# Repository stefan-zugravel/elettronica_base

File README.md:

# elettronica_base

## lab0
Keypad PCB with KiCAD

## lab1
Current sensing PCB

## lab2
Insert an FPGA in your PCB (quick preview)

## lab3
Inverter, logic gates and mux in VHDL

## lab4
Length tuning and de-skewing in KiCAD

## lab5
BCD counter in VHDL and differnt ways of dividing clock

## lab6
LTspice labs

## lab7
FIR filter and DDS compiler using FPGA

## lab8
FPGA PWM controller used for LED breathing effect

## lab9
A simple FSM in VHDL

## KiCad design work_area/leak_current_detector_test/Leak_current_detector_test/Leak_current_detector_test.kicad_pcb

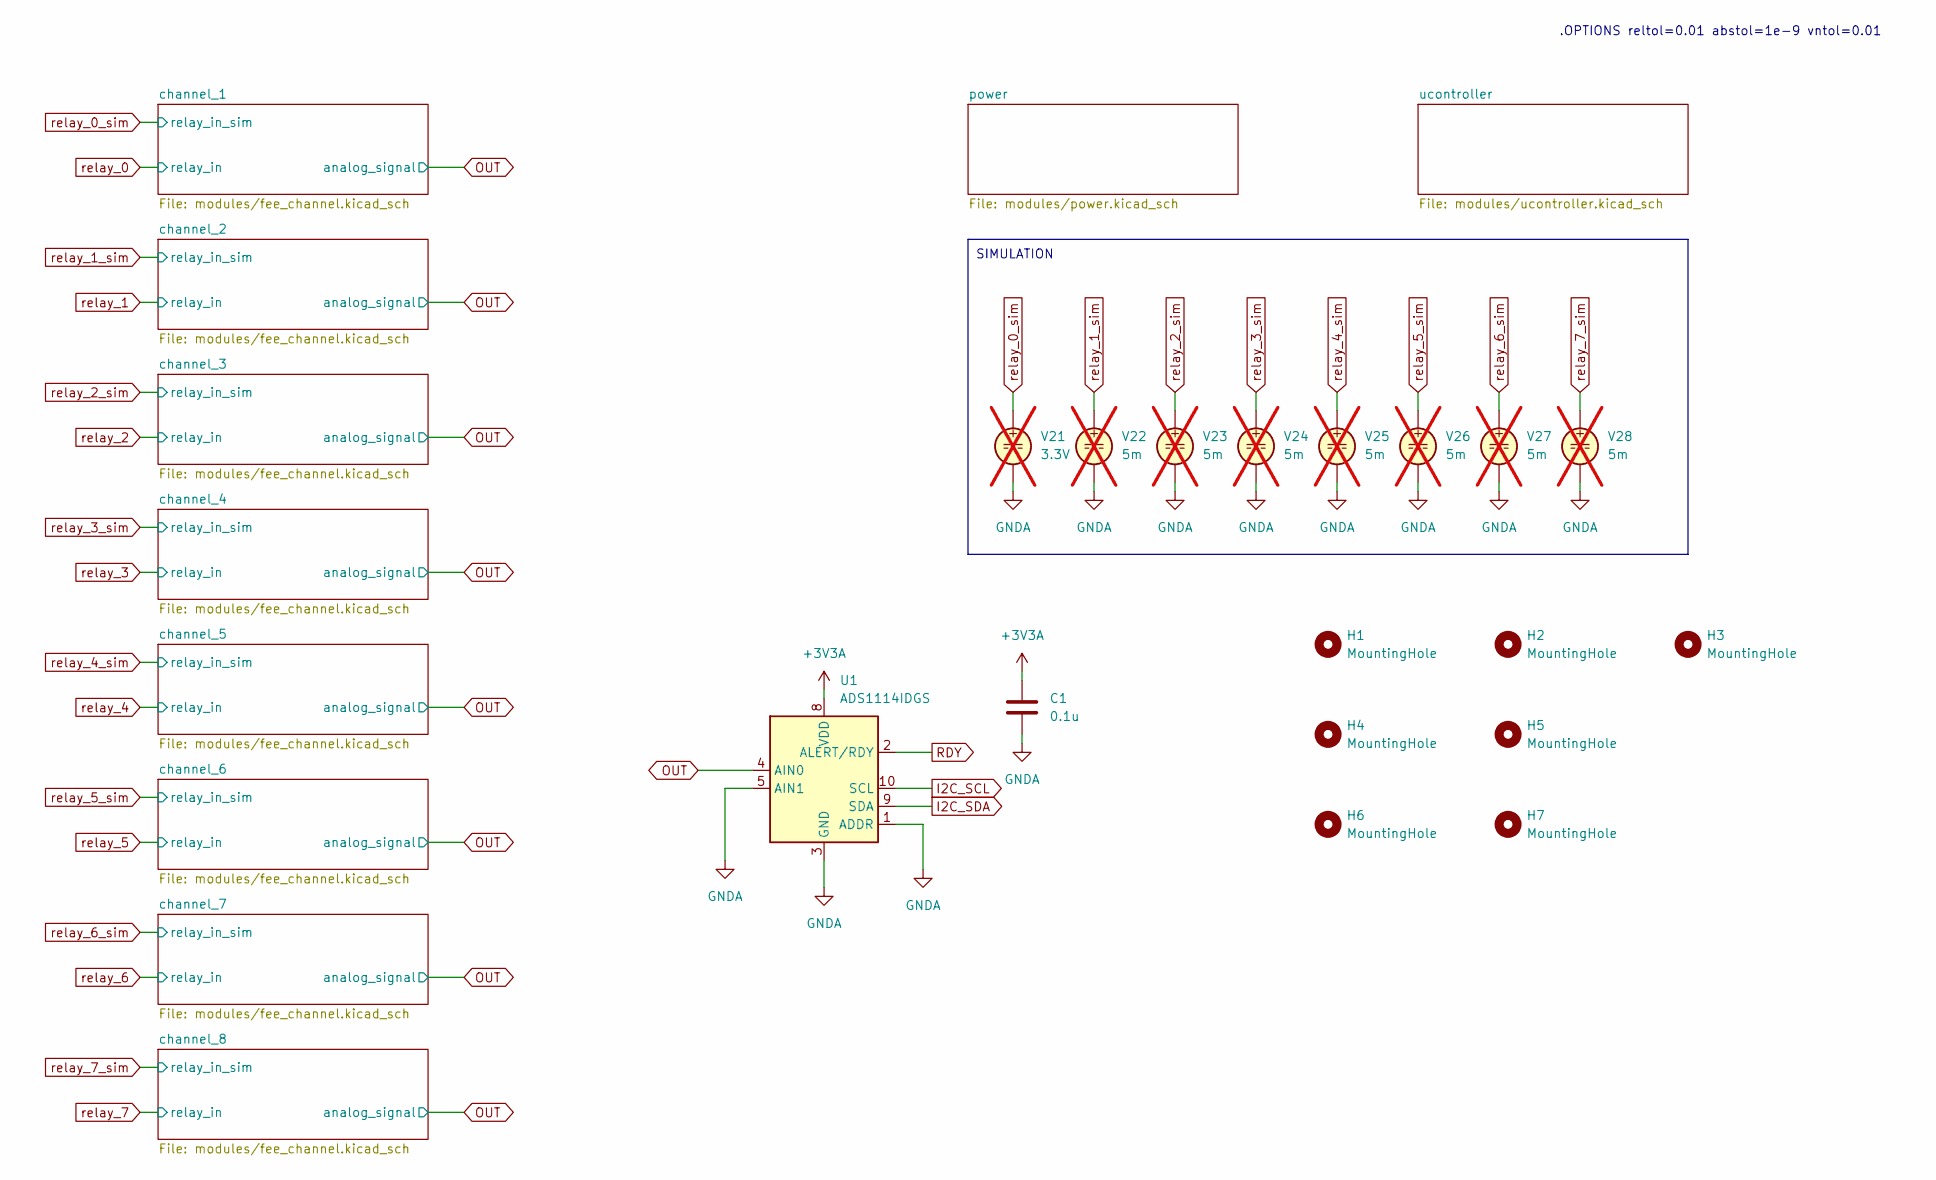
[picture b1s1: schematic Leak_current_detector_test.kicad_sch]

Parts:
C1: 0.1u; C_0603_1608Metric
H1, H2, H3: MountingHole; ToolingHole_1.152mm
H4, H5, H6, H7: MountingHole; MountingHole_3.2mm_M3
U1: ADS1114IDGS; TSSOP-10_3x3mm_P0.5mm
V21: 3.3V; not fitted
V22, V23, V24, V25, V26, V27, V28: 5m; not fitted

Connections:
+3V3A: C1.1, U1.8 (VDD); also elsewhere on the board
GNDA: C1.2, U1.1 (ADDR), U1.3 (GND), U1.5 (AIN1), V21.2, V22.2, V23.2, V24.2, V25.2, V26.2, V27.2, V28.2; also elsewhere on the board
I2C_SCL: U1.10 (SCL); also elsewhere on the board
I2C_SDA: U1.9 (SDA); also elsewhere on the board
OUT: U1.4 (AIN0); also elsewhere on the board
RDY: U1.2 (ALERT/RDY); also elsewhere on the board

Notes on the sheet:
SIMULATION
.OPTIONS reltol=0.01 abstol=1e-9 vntol=0.01

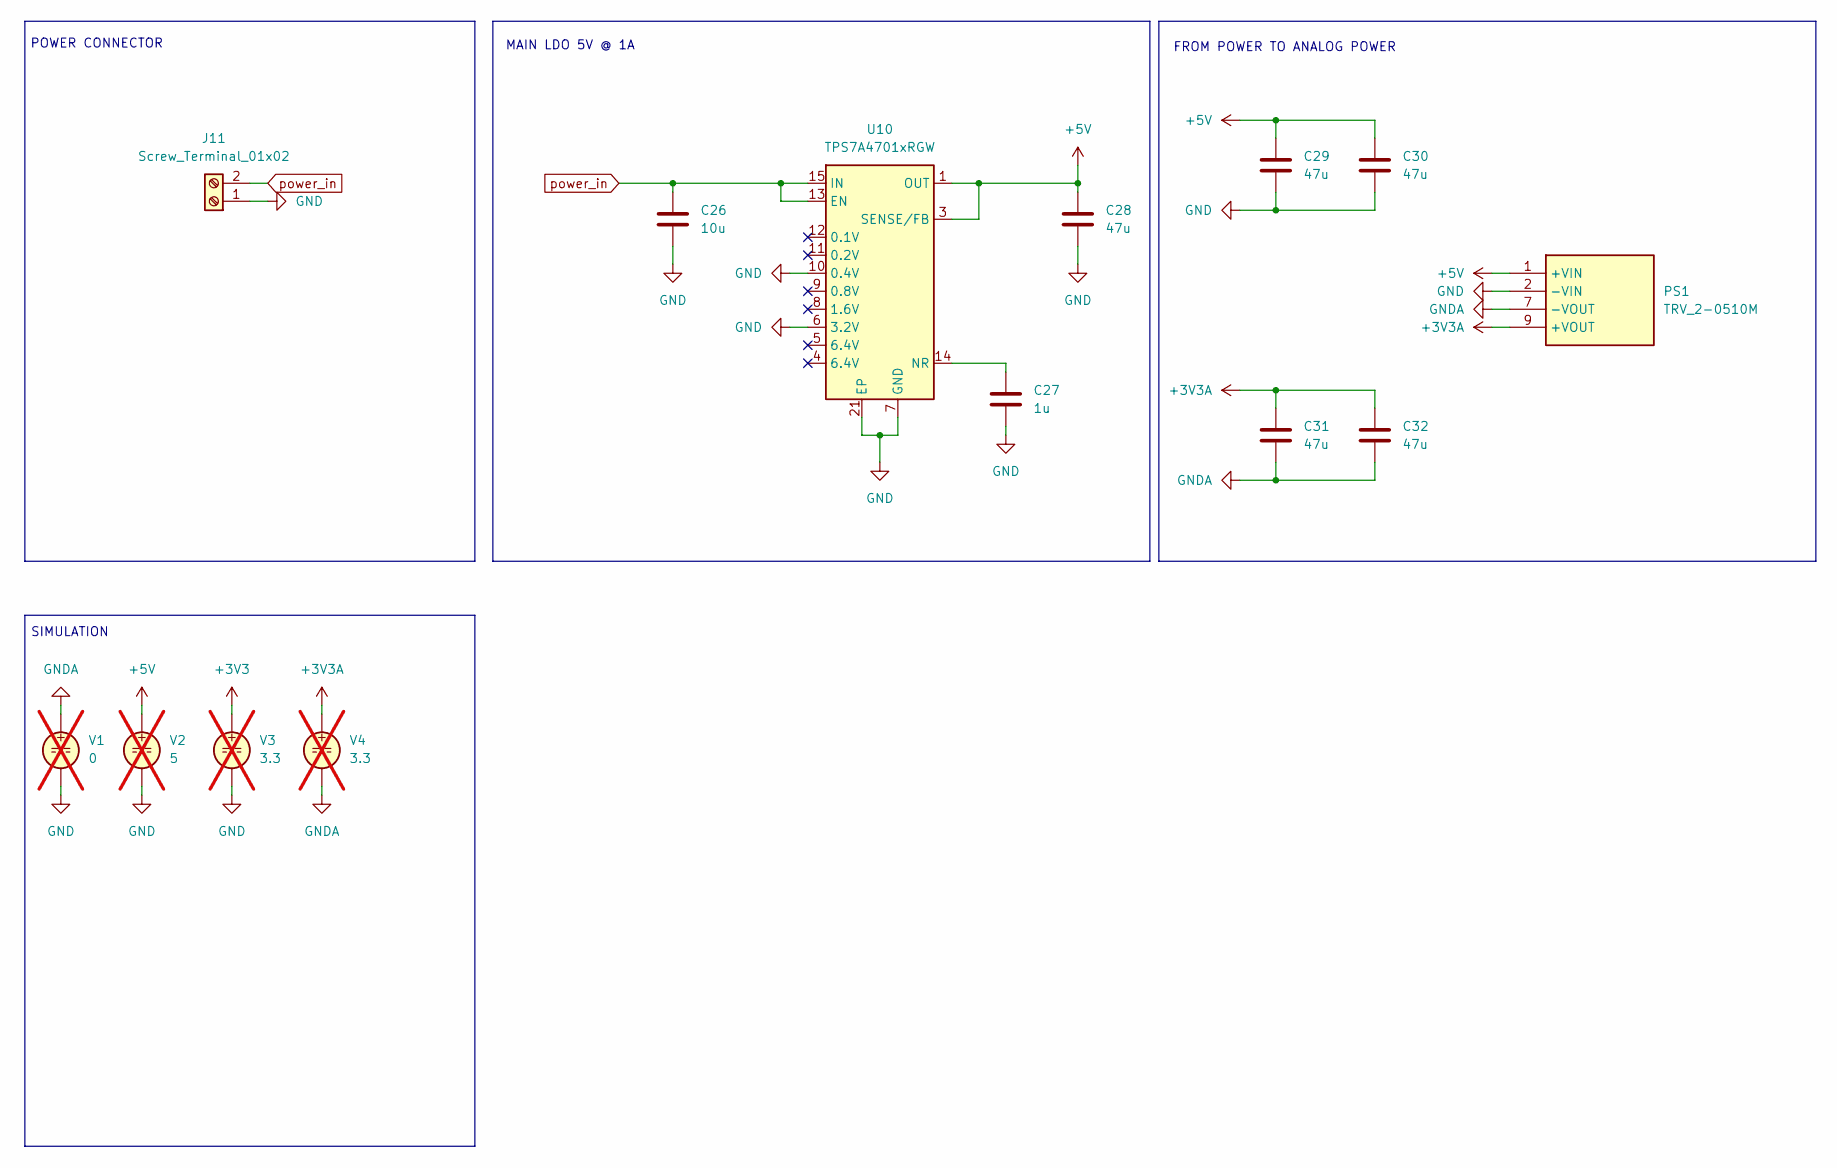
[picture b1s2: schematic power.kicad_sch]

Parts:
C26: 10u; C_0603_1608Metric
C27: 1u; C_0603_1608Metric
C28, C29, C30, C31, C32: 47u; C_0805_2012Metric
J11: Screw_Terminal_01x02; PhoenixContact_MSTBA_2,5_2-G-5,08_1x02_P5.08mm_Horizontal
PS1: TRV_2-0510M; TRV20510M; Mouser Part Number 495-TRV2-0510M
U10: TPS7A4701xRGW; Texas_RGW0020A_VQFN-20-1EP_5x5mm_P0.65mm_EP3.15x3.15mm_Ther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
V1: 0; not fitted
V2: 5; not fitted
V3, V4: 3.3; not fitted

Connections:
+3V3A: C31.1, C32.1, PS1.9 (+VOUT), V4.1; also elsewhere on the board
+5V: C28.1, C29.1, C30.1, PS1.1 (+VIN), U10.1 (OUT), U10.3 (SENSE/FB), U10.20 (OUT), V2.1; also elsewhere on the board
GND: C26.2, C27.2, C28.2, C29.2, C30.2, J11.1, PS1.2 (-VIN), U10.6 (3.2V), U10.7 (GND), U10.10 (0.4V), U10.21 (EP), V1.2, V2.2, V3.2; also elsewhere on the board
GNDA: C31.2, C32.2, PS1.7 (-VOUT), V1.1, V4.2; also elsewhere on the board
unnamed: C27.1, U10.14 (NR)
power_in: C26.1, J11.2, U10.13 (EN), U10.15 (IN), U10.16 (IN)

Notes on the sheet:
FROM POWER TO ANALOG POWER
MAIN LDO 5V @ 1A
POWER CONNECTOR
SIMULATION

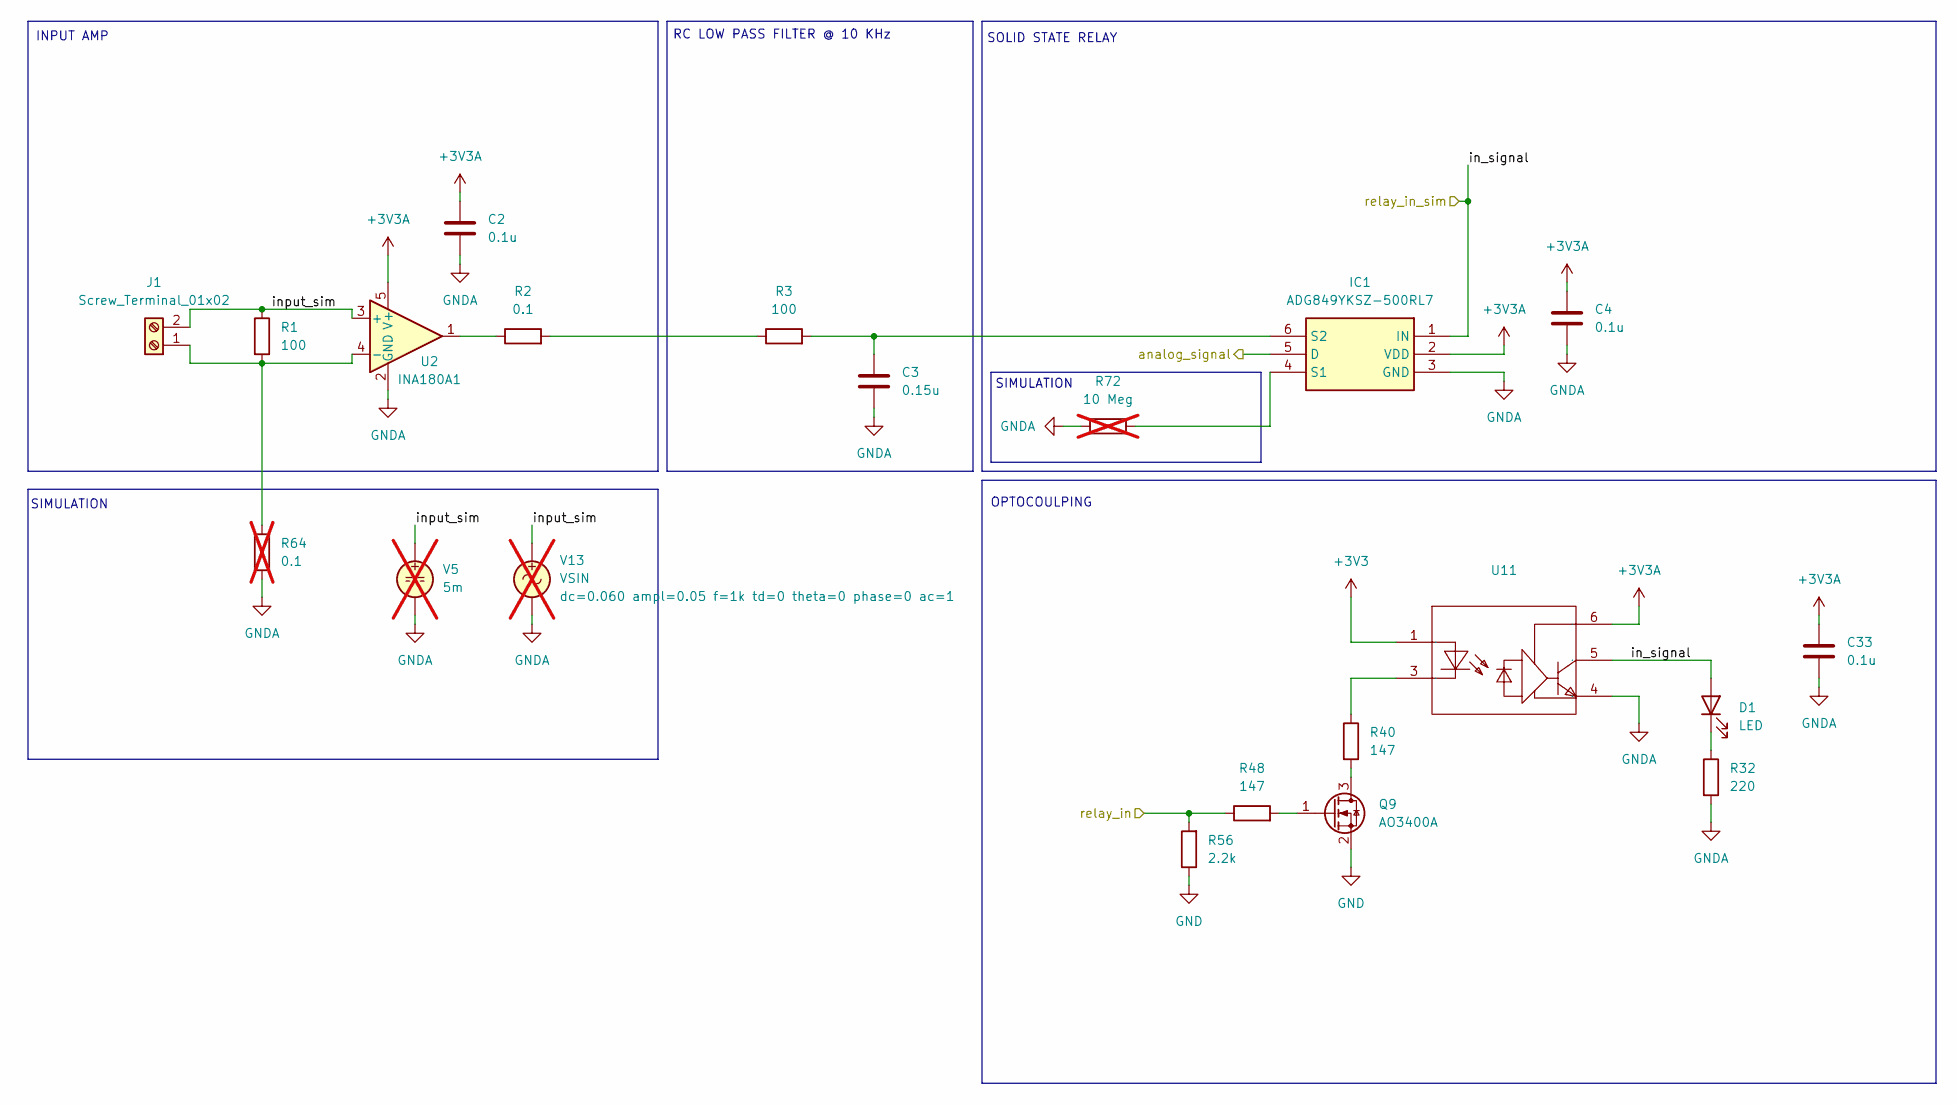
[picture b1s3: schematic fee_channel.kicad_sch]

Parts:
C2, C4, C33: 0.1u; C_0603_1608Metric
C3: 0.15u; C_0603_1608Metric
D1: LED; LED_0603_1608Metric
IC1: ADG849YKSZ-500RL7; SOT65P210X110-6N; Mouser Part Number 584-ADG849YKSZ-500R7
J1: Screw_Terminal_01x02; PhoenixContact_MCV_1,5_2-G-3.5_1x02_P3.50mm_Vertical
Q9: AO3400A; SOT-23
R1, R3: 100; R_0603_1608Metric
R2: 0.1; R_0603_1608Metric
R32: 220; R_0603_1608Metric
R40, R48: 147; R_0603_1608Metric
R56: 2.2k; R_0603_1608Metric
R64: 0.1; not fitted
R72: 10 Meg; not fitted
U2: INA180A1; SOT-23-5
U11: OPTO-SMD-5_L3.7-W4.6-P1.27-LS7.0-BR; Manufacturer Part TLP2362(TPL,E; LCSC Part Name DC输入 1通道 隔离电压(rms):3750V
V5: 5m; not fitted
V13: VSIN; not fitted

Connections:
+3V3: U11.1; also elsewhere on the board
+3V3A: C2.1, C4.1, C33.1, IC1.2 (VDD), U2.5 (V+), U11.6; also elsewhere on the board
/channel_1/input_sim: J1.2, R1.1, U2.3 (+)
GND: Q9.2 (S), R56.1; also elsewhere on the board
GNDA: C2.2, C3.2, C4.2, C33.2, IC1.3 (GND), R32.2, R64.2, R72.1, U2.2 (GND), U11.4, V5.2, V13.2; also elsewhere on the board
unnamed: D1.1 (K), R32.1
unnamed: C3.1, IC1.6 (S2), R3.2
unnamed: J1.1, R1.2, U2.4 (-)
unnamed: Q9.3 (D), R40.2
unnamed: Q9.1 (G), R48.2
unnamed: R2.1, U2.1
unnamed: R2.2, R3.1
unnamed: R40.1, U11.3
OUT: IC1.5 (D); also elsewhere on the board
relay_0: R48.1, R56.2; also elsewhere on the board
relay_0_sim: D1.2 (A), IC1.1 (IN), U11.5

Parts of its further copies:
C5, C7, C8, C10, C11, C13, C14, C16, C17, C19, C20, C22, C23, C25, C34, C35, C36, C37, C38, C39, C40: 0.1u; C_0603_1608Metric
C6, C9, C12, C15, C18, C21, C24: 0.15u; C_0603_1608Metric
D2, D3, D4, D5, D6, D7, D8: LED; LED_0603_1608Metric
IC2, IC3, IC4, IC5, IC6, IC7, IC8: ADG849YKSZ-500RL7; SOT65P210X110-6N; Mouser Part Number 584-ADG849YKSZ-500R7
J2, J3, J4, J5, J6, J7, J8: Screw_Terminal_01x02; PhoenixContact_MCV_1,5_2-G-3.5_1x02_P3.50mm_Vertical
Q10, Q11, Q12, Q13, Q14, Q15, Q16: AO3400A; SOT-23
R4, R6, R7, R9, R10, R12, R13, R15, R16, R18, R19, R21, R22, R24: 100; R_0603_1608Metric
R5, R8, R11, R14, R17, R20, R23: 0.1; R_0603_1608Metric
R33, R34, R35, R36, R37, R38, R39: 220; R_0603_1608Metric
R41, R42, R43, R44, R45, R46, R47, R49, R50, R51, R52, R53, R54, R55: 147; R_0603_1608Metric
R57, R58, R59, R60, R61, R62, R63: 2.2k; R_0603_1608Metric
U3, U4, U5, U6, U7, U8, U9: INA180A1; SOT-23-5
U12, U13, U14, U15, U16, U17, U18: OPTO-SMD-5_L3.7-W4.6-P1.27-LS7.0-BR; Manufacturer Part TLP2362(TPL,E; LCSC Part Name DC输入 1通道 隔离电压(rms):3750V

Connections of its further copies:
+3V3: U12.1, U13.1, U14.1, U15.1, U16.1, U17.1, U18.1; also elsewhere on the board
+3V3A: C5.1, C7.1, C8.1, C10.1, C11.1, C13.1, C14.1, C16.1, C17.1, C19.1, C20.1, C22.1, C23.1, C25.1, C34.1, C35.1, C36.1, C37.1, C38.1, C39.1, C40.1, IC2.2 (VDD), IC3.2 (VDD), IC4.2 (VDD), IC5.2 (VDD), IC6.2 (VDD), IC7.2 (VDD), IC8.2 (VDD), U3.5 (V+), U4.5 (V+), U5.5 (V+), U6.5 (V+), U7.5 (V+), U8.5 (V+), U9.5 (V+), U12.6, U13.6, U14.6, U15.6, U16.6, U17.6, U18.6; also elsewhere on the board
/channel_2/input_sim: J2.2, R4.1, U3.3 (+)
/channel_3/input_sim: J3.2, R7.1, U4.3 (+)
/channel_4/input_sim: J4.2, R10.1, U5.3 (+)
/channel_5/input_sim: J5.2, R13.1, U6.3 (+)
/channel_6/input_sim: J6.2, R16.1, U7.3 (+)
/channel_7/input_sim: J7.2, R19.1, U8.3 (+)
/channel_8/input_sim: J8.2, R22.1, U9.3 (+)
GND: Q10.2 (S), Q11.2 (S), Q12.2 (S), Q13.2 (S), Q14.2 (S), Q15.2 (S), Q16.2 (S), R57.1, R58.1, R59.1, R60.1, R61.1, R62.1, R63.1; also elsewhere on the board
GNDA: C5.2, C6.2, C7.2, C8.2, C9.2, C10.2, C11.2, C12.2, C13.2, C14.2, C15.2, C16.2, C17.2, C18.2, C19.2, C20.2, C21.2, C22.2, C23.2, C24.2, C25.2, C34.2, C35.2, C36.2, C37.2, C38.2, C39.2, C40.2, IC2.3 (GND), IC3.3 (GND), IC4.3 (GND), IC5.3 (GND), IC6.3 (GND), IC7.3 (GND), IC8.3 (GND), R33.2, R34.2, R35.2, R36.2, R37.2, R38.2, R39.2, U3.2 (GND), U4.2 (GND), U5.2 (GND), U6.2 (GND), U7.2 (GND), U8.2 (GND), U9.2 (GND), U12.4, U13.4, U14.4, U15.4, U16.4, U17.4, U18.4; also elsewhere on the board
unnamed: D2.1 (K), R33.1
unnamed: D3.1 (K), R34.1
unnamed: D4.1 (K), R35.1
unnamed: D5.1 (K), R36.1
unnamed: D6.1 (K), R37.1
unnamed: D7.1 (K), R38.1
unnamed: D8.1 (K), R39.1
unnamed: C6.1, IC2.6 (S2), R6.2
unnamed: C9.1, IC3.6 (S2), R9.2
unnamed: C12.1, IC4.6 (S2), R12.2
unnamed: C15.1, IC5.6 (S2), R15.2
unnamed: C18.1, IC6.6 (S2), R18.2
unnamed: C21.1, IC7.6 (S2), R21.2
unnamed: C24.1, IC8.6 (S2), R24.2
unnamed: J2.1, R4.2, U3.4 (-)
unnamed: J3.1, R7.2, U4.4 (-)
unnamed: J4.1, R10.2, U5.4 (-)
unnamed: J5.1, R13.2, U6.4 (-)
unnamed: J6.1, R16.2, U7.4 (-)
unnamed: J7.1, R19.2, U8.4 (-)
unnamed: J8.1, R22.2, U9.4 (-)
unnamed: Q10.3 (D), R41.2
unnamed: Q10.1 (G), R49.2
unnamed: Q11.3 (D), R42.2
unnamed: Q11.1 (G), R50.2
unnamed: Q12.3 (D), R43.2
unnamed: Q12.1 (G), R51.2
unnamed: Q13.3 (D), R44.2
unnamed: Q13.1 (G), R52.2
unnamed: Q14.3 (D), R45.2
unnamed: Q14.1 (G), R53.2
unnamed: Q15.3 (D), R46.2
unnamed: Q15.1 (G), R54.2
unnamed: Q16.3 (D), R47.2
unnamed: Q16.1 (G), R55.2
unnamed: R5.1, U3.1
unnamed: R5.2, R6.1
unnamed: R8.1, U4.1
unnamed: R8.2, R9.1
unnamed: R11.1, U5.1
unnamed: R11.2, R12.1
unnamed: R14.1, U6.1
unnamed: R14.2, R15.1
unnamed: R17.1, U7.1
unnamed: R17.2, R18.1
unnamed: R20.1, U8.1
unnamed: R20.2, R21.1
unnamed: R23.1, U9.1
unnamed: R23.2, R24.1
unnamed: R41.1, U12.3
unnamed: R42.1, U13.3
unnamed: R43.1, U14.3
unnamed: R44.1, U15.3
unnamed: R45.1, U16.3
unnamed: R46.1, U17.3
unnamed: R47.1, U18.3
OUT: IC2.5 (D), IC3.5 (D), IC4.5 (D), IC5.5 (D), IC6.5 (D), IC7.5 (D), IC8.5 (D); also elsewhere on the board
relay_1: R49.1, R57.2; also elsewhere on the board
relay_1_sim: D2.2 (A), IC2.1 (IN), U12.5
relay_2: R50.1, R58.2; also elsewhere on the board
relay_2_sim: D3.2 (A), IC3.1 (IN), U13.5
relay_3: R51.1, R59.2; also elsewhere on the board
relay_3_sim: D4.2 (A), IC4.1 (IN), U14.5
relay_4: R52.1, R60.2; also elsewhere on the board
relay_4_sim: D5.2 (A), IC5.1 (IN), U15.5
relay_5: R53.1, R61.2; also elsewhere on the board
relay_5_sim: D6.2 (A), IC6.1 (IN), U16.5
relay_6: R54.1, R62.2; also elsewhere on the board
relay_6_sim: D7.2 (A), IC7.1 (IN), U17.5
relay_7: R55.1, R63.2; also elsewhere on the board
relay_7_sim: D8.2 (A), IC8.1 (IN), U18.5

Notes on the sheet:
SIMULATION
RC LOW PASS FILTER @ 10 KHz
INPUT AMP
SOLID STATE RELAY
OPTOCOULPING

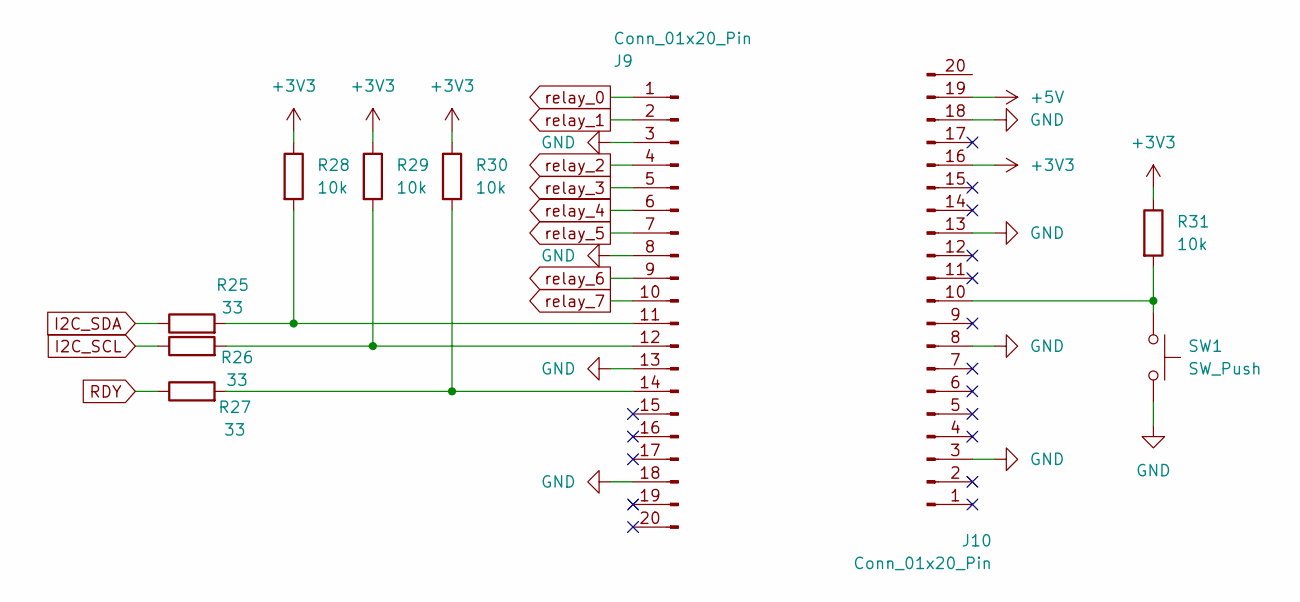
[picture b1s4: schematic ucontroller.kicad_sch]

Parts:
J9, J10: Conn_01x20_Pin; PinHeader_1x20_P2.54mm_Vertical
R25, R26, R27: 33; R_0603_1608Metric
R28, R29, R30, R31: 10k; R_0603_1608Metric
SW1: SW_Push; SW_PUSH_6mm_H5mm

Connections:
+3V3: J10.16, R28.1, R29.1, R30.1, R31.1; also elsewhere on the board
+5V: J10.19; also elsewhere on the board
GND: J9.3, J9.8, J9.13, J9.18, J10.3, J10.8, J10.13, J10.18, SW1.2; also elsewhere on the board
I2C_SCL: R26.1; also elsewhere on the board
I2C_SDA: R25.1; also elsewhere on the board
unnamed: J9.11, R25.2, R28.2
unnamed: J9.12, R26.2, R29.2
unnamed: J9.14, R27.2, R30.2
unnamed: J10.10, R31.2, SW1.1
RDY: R27.1; also elsewhere on the board
relay_0: J9.1; also elsewhere on the board
relay_1: J9.2; also elsewhere on the board
relay_2: J9.4; also elsewhere on the board
relay_3: J9.5; also elsewhere on the board
relay_4: J9.6; also elsewhere on the board
relay_5: J9.7; also elsewhere on the board
relay_6: J9.9; also elsewhere on the board
relay_7: J9.10; also elsewhere on the board

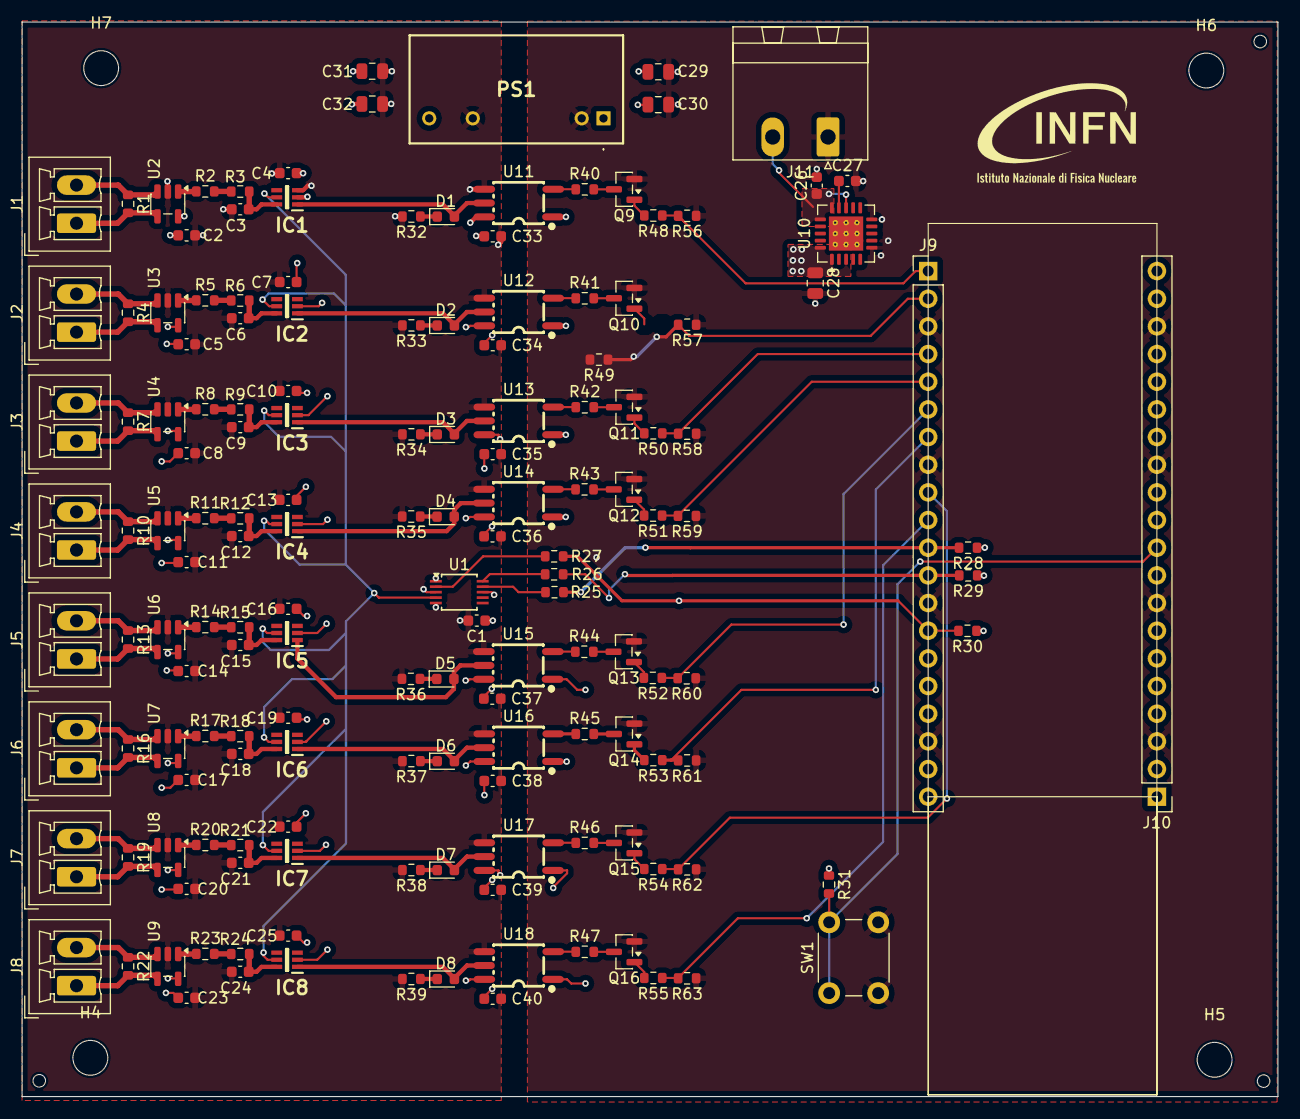
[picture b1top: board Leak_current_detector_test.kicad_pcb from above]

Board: 6 copper layers, 115.3 x 98.7 mm, 165 parts (0 on the bottom side), 103 nets.

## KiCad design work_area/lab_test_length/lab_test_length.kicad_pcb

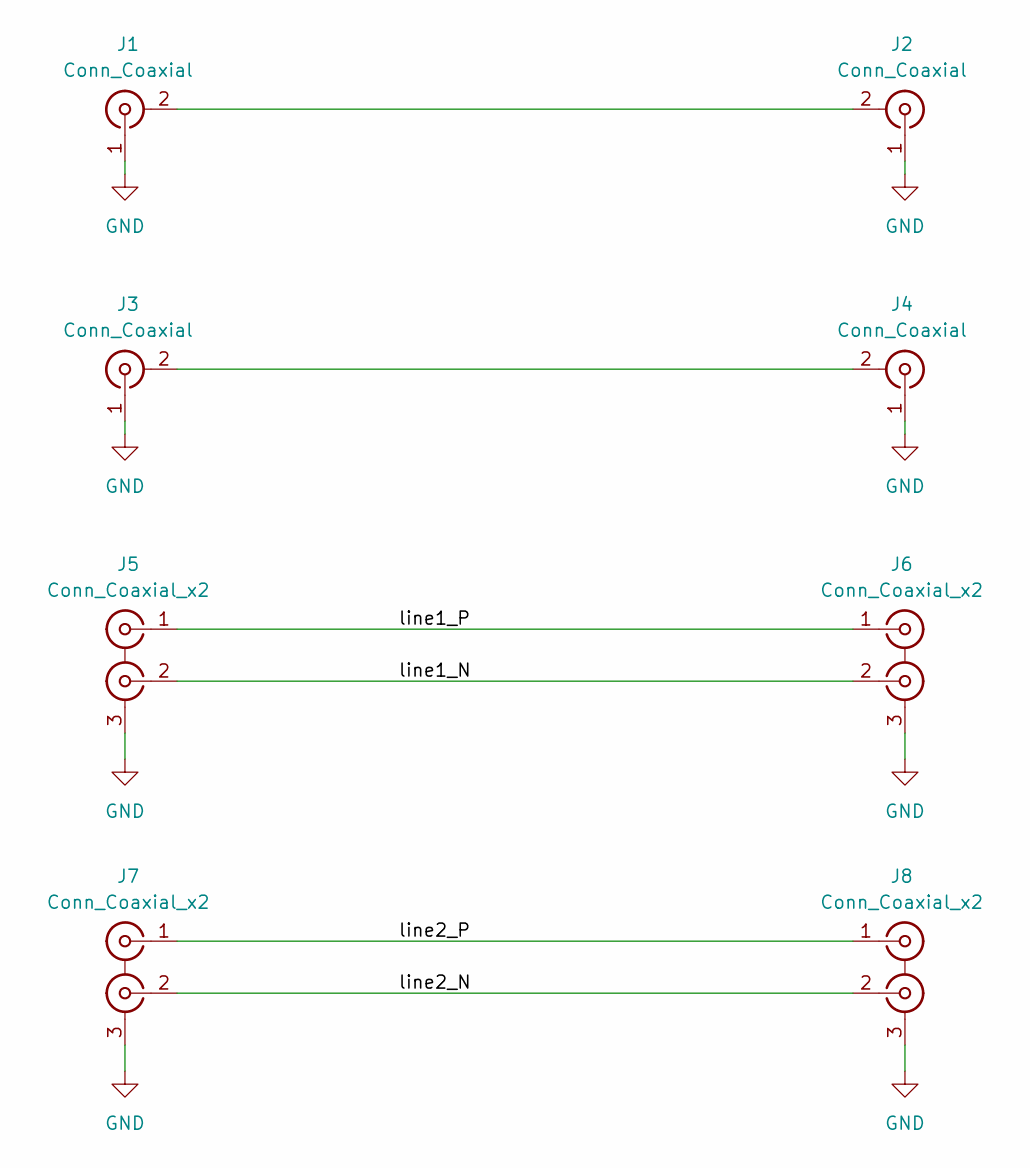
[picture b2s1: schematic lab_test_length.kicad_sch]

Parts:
J1, J2, J3, J4: Conn_Coaxial; MMCX_Molex_73415-0961_Horizontal_1.0mm-PCB
J5, J6, J7, J8: Conn_Coaxial_x2; LEMO-EPG.00.302.NLN

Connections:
/line1_N: J5.2 (IN2), J6.2 (IN2)
/line1_P: J5.1 (IN1), J6.1 (IN1)
/line2_N: J7.2 (IN2), J8.2 (IN2)
/line2_P: J7.1 (IN1), J8.1 (IN1)
GND: J1.1 (In), J2.1 (In), J3.1 (In), J4.1 (In), J5.3 (EXT), J6.3 (EXT), J7.3 (EXT), J8.3 (EXT)
unnamed: J1.2 (Ext), J2.2 (Ext)
unnamed: J3.2 (Ext), J4.2 (Ext)

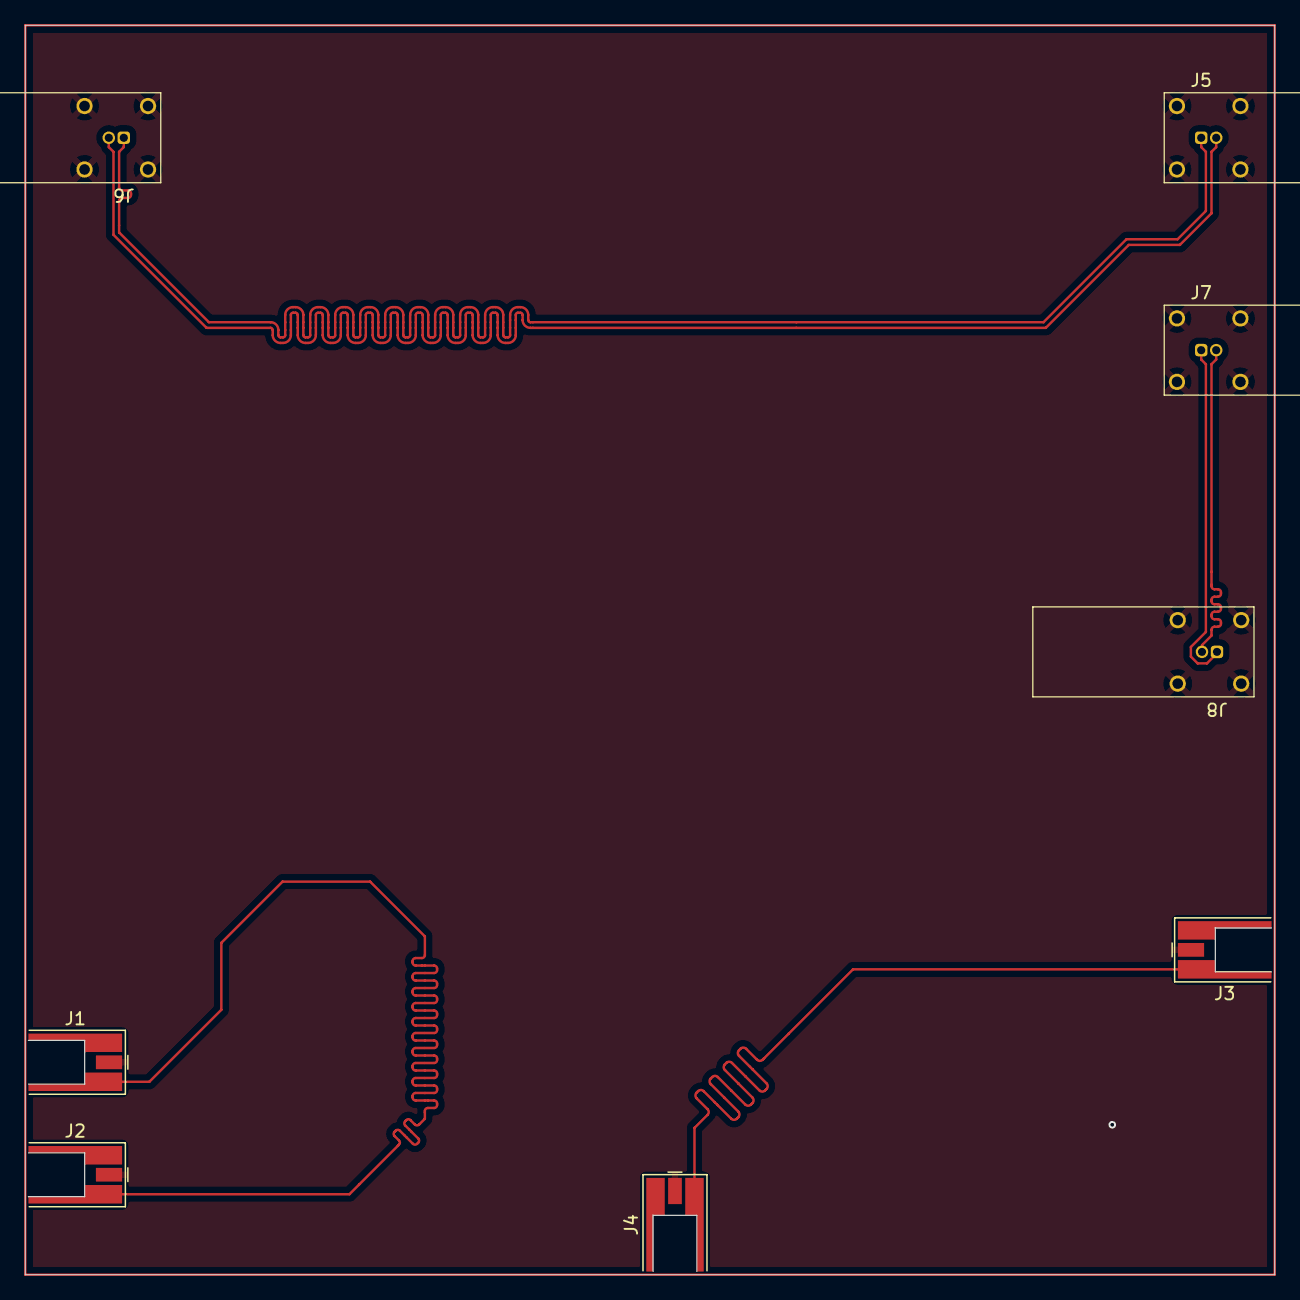
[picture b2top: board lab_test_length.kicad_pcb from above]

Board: 2 copper layers, 99.9 x 99.9 mm, 8 parts (0 on the bottom side), 7 nets.

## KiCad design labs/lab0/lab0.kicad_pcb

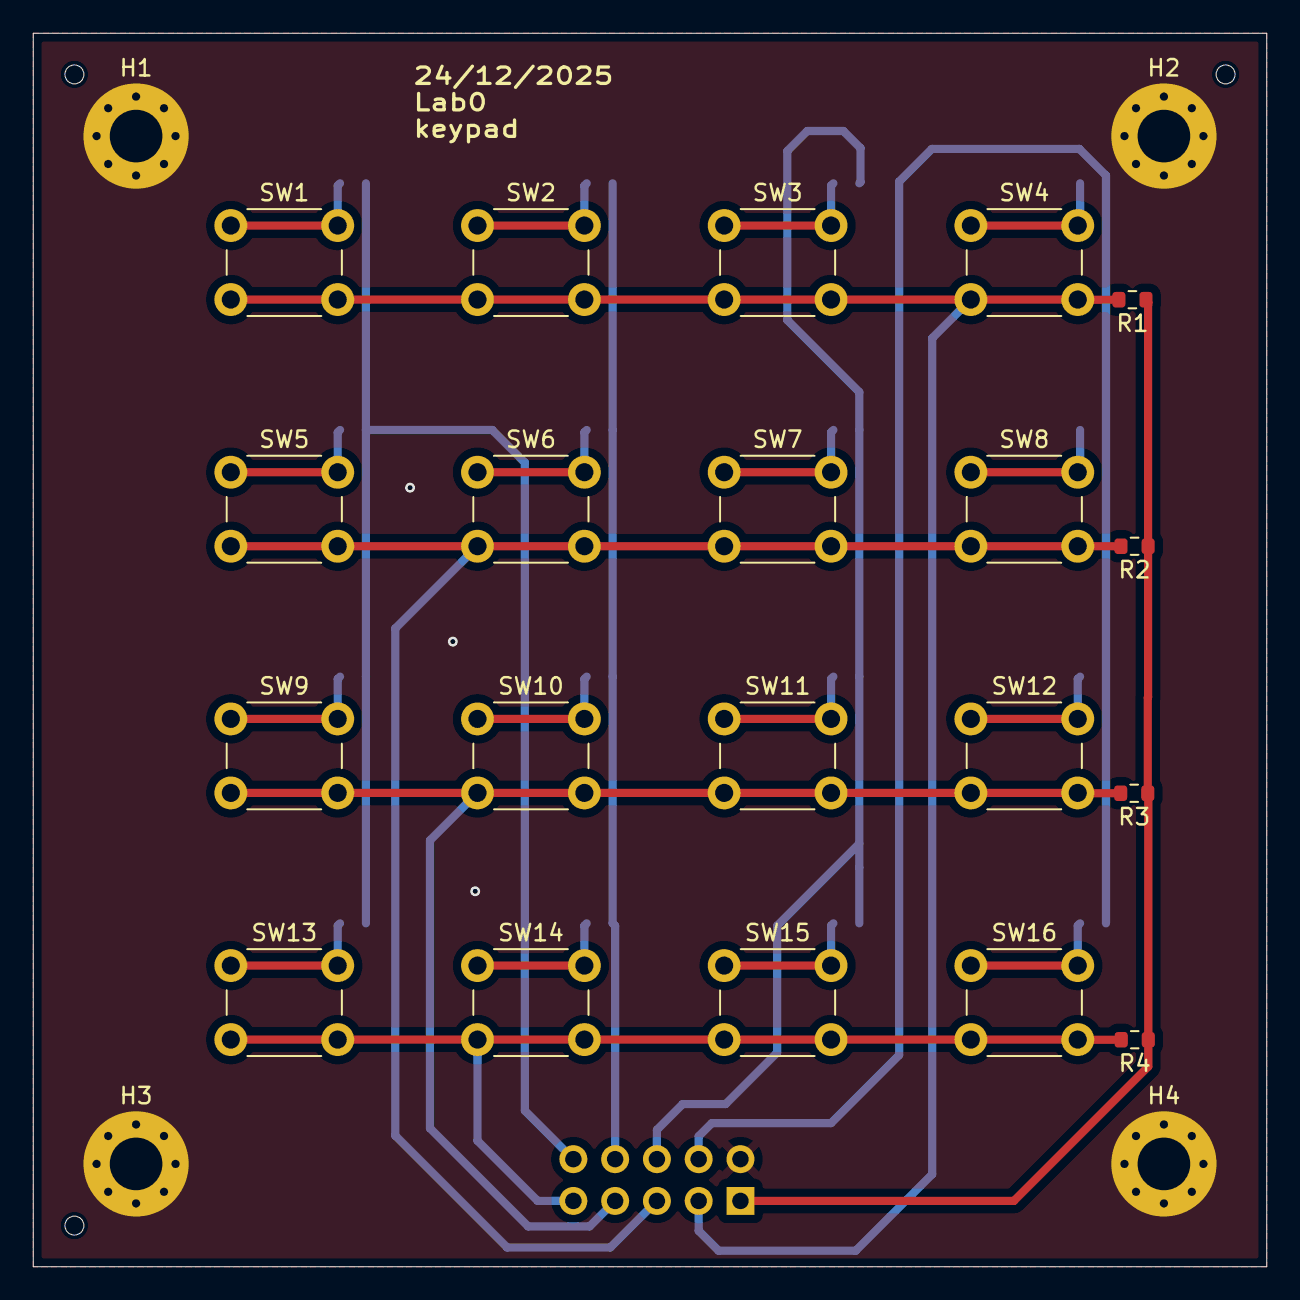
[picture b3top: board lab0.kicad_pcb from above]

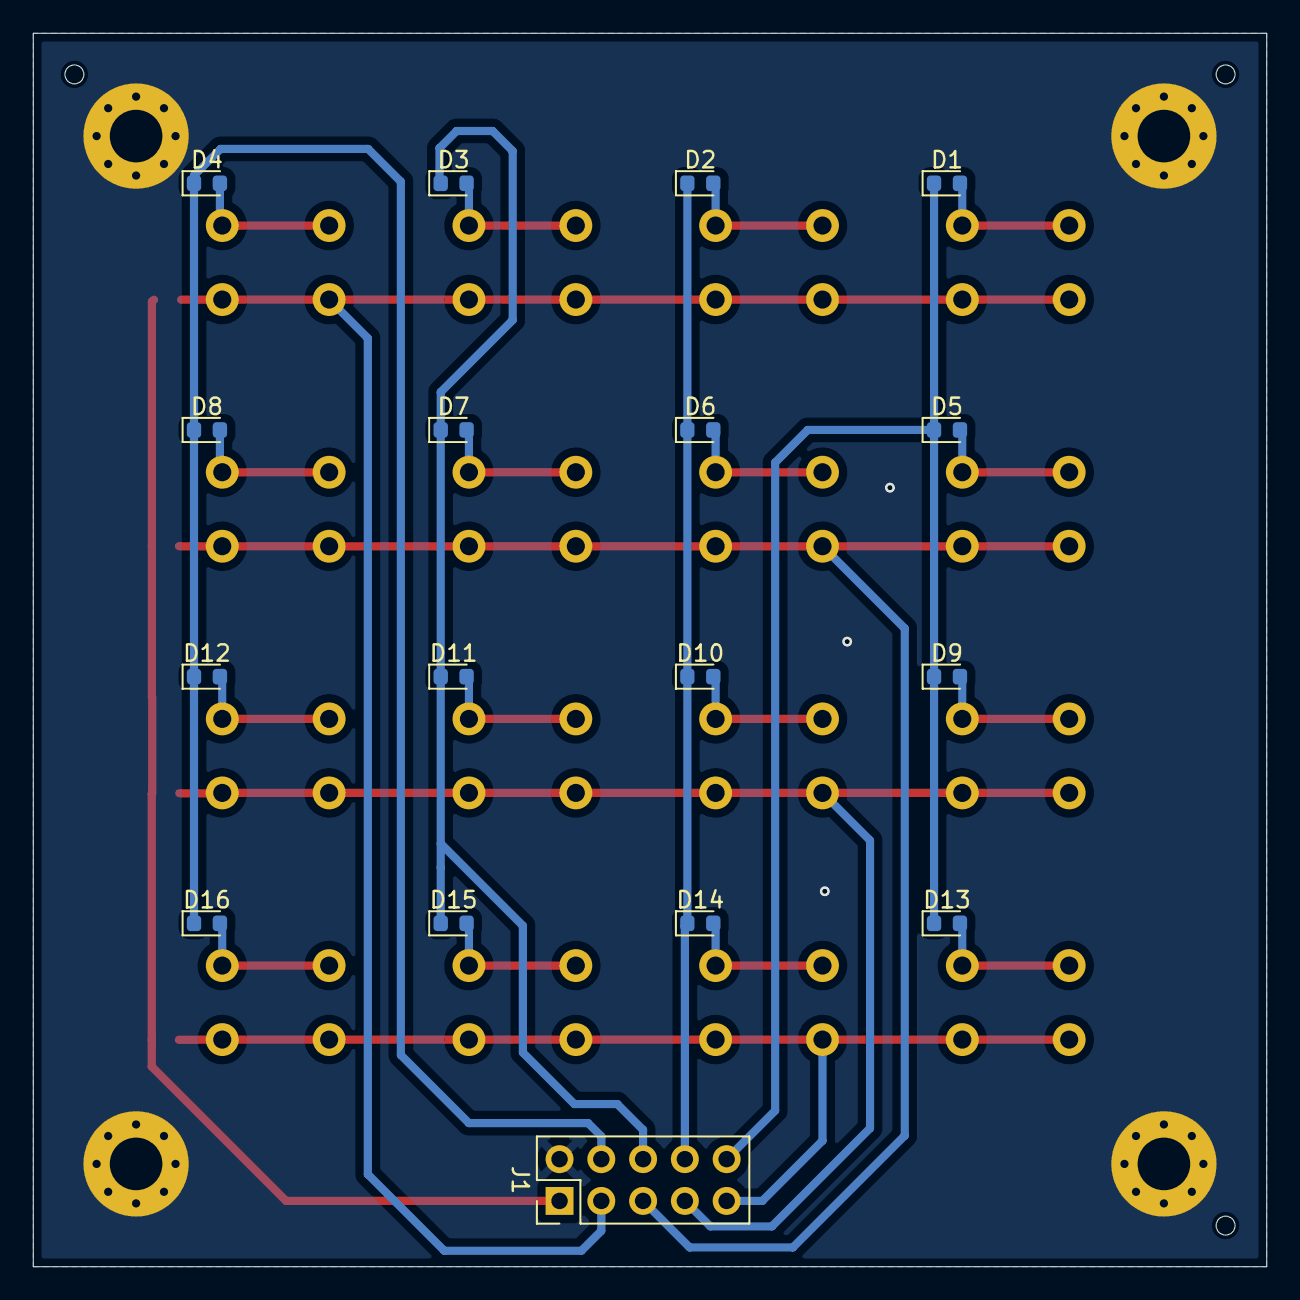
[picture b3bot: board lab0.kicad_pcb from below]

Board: 2 copper layers, 75.0 x 75.0 mm, 44 parts (17 on the bottom side), 26 nets.

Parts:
D1, D2, D3, D4, D5, D6, D7, D8, D9, D10, D11, D12, D13, D14, D15, D16: D; D_0603_1608Metric
H1, H2, H3, H4: MountingHole_Pad; MountingHole_3.2mm_M3_Pad_Via
H5, H6, H7: MountingHole; ToolingHole_1.152mm
J1: Conn_02x05_Odd_Even; PinHeader_2x05_P2.54mm_Vertical
R1, R2, R3, R4: 10k; R_0603_1608Metric
SW1, SW2, SW3, SW4, SW5, SW6, SW7, SW8, SW9, SW10, SW11, SW12, SW13, SW14, SW15, SW16: SW_Omron_B3FS; SW_PUSH_6mm

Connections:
COL_1: J1.3, R1.2, SW1.2, SW2.2, SW3.2, SW4.2
COL_2: J1.5, R2.2, SW5.2, SW6.2, SW7.2, SW8.2
COL_3: J1.7, R3.2, SW9.2, SW10.2, SW11.2, SW12.2
COL_4: J1.9, R4.2, SW13.2, SW14.2, SW15.2, SW16.2
GND: H1.1, H2.1, H3.1, H4.1, J1.2
unnamed: D1.2 (A), SW1.1
unnamed: D2.2 (A), SW2.1
unnamed: D3.2 (A), SW3.1
unnamed: D4.2 (A), SW4.1
unnamed: D5.2 (A), SW5.1
unnamed: D6.2 (A), SW6.1
unnamed: D7.2 (A), SW7.1
unnamed: D8.2 (A), SW8.1
unnamed: D9.2 (A), SW9.1
unnamed: D10.2 (A), SW10.1
unnamed: D11.2 (A), SW11.1
unnamed: D12.2 (A), SW12.1
unnamed: D13.2 (A), SW13.1
unnamed: D14.2 (A), SW14.1
unnamed: D15.2 (A), SW15.1
unnamed: D16.2 (A), SW16.1
RAW_1: D1.1 (K), D5.1 (K), D9.1 (K), D13.1 (K), J1.10
RAW_2: D2.1 (K), D6.1 (K), D10.1 (K), D14.1 (K), J1.8
RAW_3: D3.1 (K), D7.1 (K), D11.1 (K), D15.1 (K), J1.6
RAW_4: D4.1 (K), D8.1 (K), D12.1 (K), D16.1 (K), J1.4
VCC: J1.1, R1.1, R2.1, R3.1, R4.1

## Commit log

2025-12-22 init
2025-12-22 added lab0
2025-12-22 added empty lab1
2025-12-24 lab0 finished
2025-12-24 added lab2
2025-12-25 added lab1
2025-12-25 added lab3
2025-12-25 added lab4
2025-12-26 working on slides
2025-12-26 commit from windows
2025-12-26 slides work
2025-12-29 added lab5
2026-01-07 working on lab5
2026-01-08 added lab7
2026-01-08 working on lab6
2026-01-09 added lab8
2026-01-09 added vcd and tcl
2026-01-09 work on lab6
2026-01-10 add git commands
2026-01-10 add README and pcb documentation
2026-01-12 ADD pdfs and jlcpcb stackups
2026-01-12 work on lection 1
2026-01-13 Add lab9
2026-01-13 Add lab9 gif image
2026-01-14 update sildes
2026-01-15 ADD AGD849
2026-01-15 modify slide lezione4
2026-01-19 ADD schematic w55rp20
2026-01-19 ADD vhdl reserved words
2026-01-21 minor revision
2026-01-22 ADD lab files
